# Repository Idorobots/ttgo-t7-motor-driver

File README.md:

# TTGO T7-based DC motor driver board

This is an interface board that adds four DC motor drivers, three servo connectors and I2C breakout to TTGO T7. 
You can use it to build a drone. :shrug:

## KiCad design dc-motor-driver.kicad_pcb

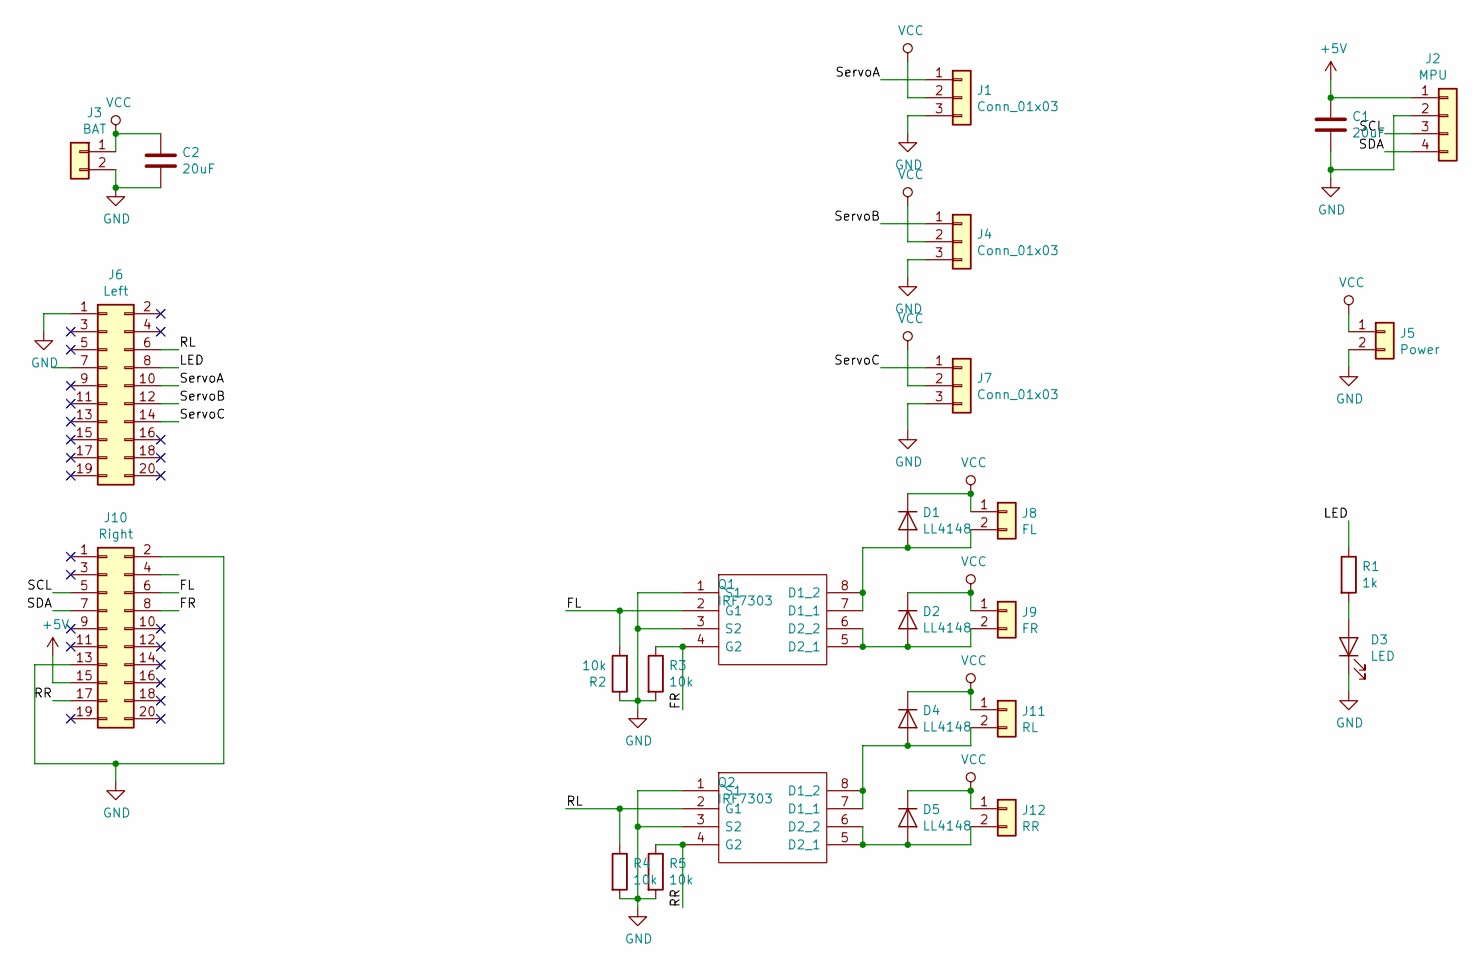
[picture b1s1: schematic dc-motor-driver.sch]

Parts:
C1: 20uF; C_1206_3216Metric_Pad1.42x1.75mm_HandSolder
C2: 20uF; CP_EIA-3528-21_Kemet-B_Pad1.50x2.35mm_HandSolder
D1, D2, D4, D5: LL4148; D_MiniMELF
D3: LED; LED_1206_3216Metric_Pad1.42x1.75mm_HandSolder
J1, J4, J7: Conn_01x03; PinHeader_1x03_P2.54mm_Vertical
J2: MPU; PinHeader_1x04_P2.54mm_Vertical
J3: BAT; JST_XH_S2B-XH-A-1_1x02_P2.50mm_Horizontal
J5: Power; PinHeader_1x02_P2.54mm_Vertical
J6: Left; PinHeader_2x10_P2.54mm_Vertical
J8: FL; Molex_PicoBlade_53398-0271_1x02-1MP_P1.25mm_Vertical
J9: FR; Molex_PicoBlade_53398-0271_1x02-1MP_P1.25mm_Vertical
J10: Right; PinHeader_2x10_P2.54mm_Vertical
J11: RL; Molex_PicoBlade_53398-0271_1x02-1MP_P1.25mm_Vertical
J12: RR; Molex_PicoBlade_53398-0271_1x02-1MP_P1.25mm_Vertical
Q1, Q2: IRF7303; SOIC-8_3.9x4.9mm_P1.27mm
R1: 1k; R_1206_3216Metric
R2, R3, R4, R5: 10k; R_1206_3216Metric

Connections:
+5V: C1.1, J2.1, J10.15
/FL: J10.6, Q1.2 (G1), R2.2
/FR: J10.8, Q1.4 (G2), R3.1
/LED: J6.8, R1.1
/RL: J6.6, Q2.2 (G1), R4.1
/RR: J10.17, Q2.4 (G2), R5.1
/SCL: J2.3, J10.5
/SDA: J2.4, J10.7
/ServoA: J1.1, J6.10
/ServoB: J4.1, J6.12
/ServoC: J6.14, J7.1
GND: C1.2, C2.2, D3.1 (K), J1.3, J2.2, J3.2, J4.3, J5.2, J6.1, J7.3, J8.MP, J9.MP, J10.2, J10.13, J11.MP, J12.MP, Q1.1 (S1), Q1.3 (S2), Q2.1 (S1), Q2.3 (S2), R2.1, R3.2, R4.2, R5.2
unnamed: D1.2 (A), J8.2, Q1.7 (D1_1), Q1.8 (D1_2)
unnamed: D2.2 (A), J9.2, Q1.5 (D2_1), Q1.6 (D2_2)
unnamed: D3.2 (A), R1.2
unnamed: D4.2 (A), J11.2, Q2.7 (D1_1), Q2.8 (D1_2)
unnamed: D5.2 (A), J12.2, Q2.5 (D2_1), Q2.6 (D2_2)
VCC: C2.1, D1.1 (K), D2.1 (K), D4.1 (K), D5.1 (K), J1.2, J3.1, J4.2, J5.1, J7.2, J8.1, J9.1, J11.1, J12.1

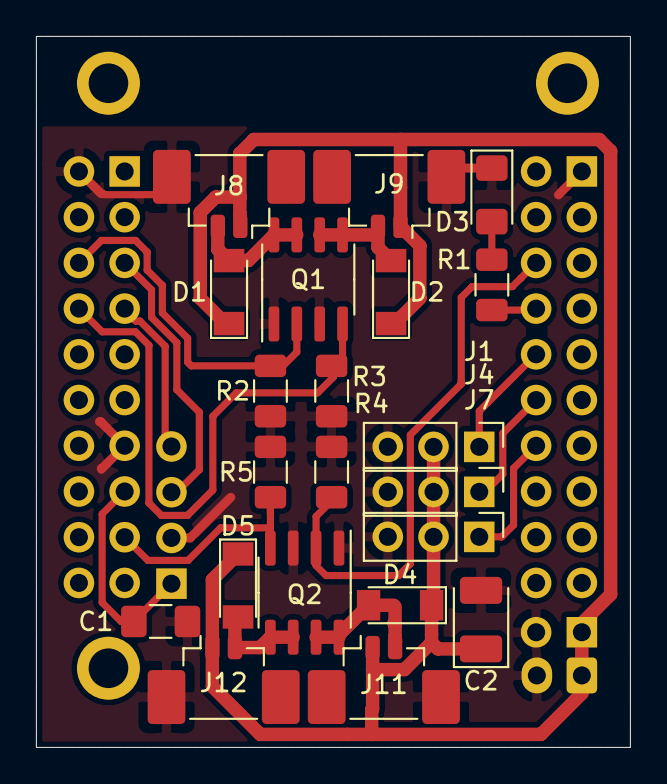
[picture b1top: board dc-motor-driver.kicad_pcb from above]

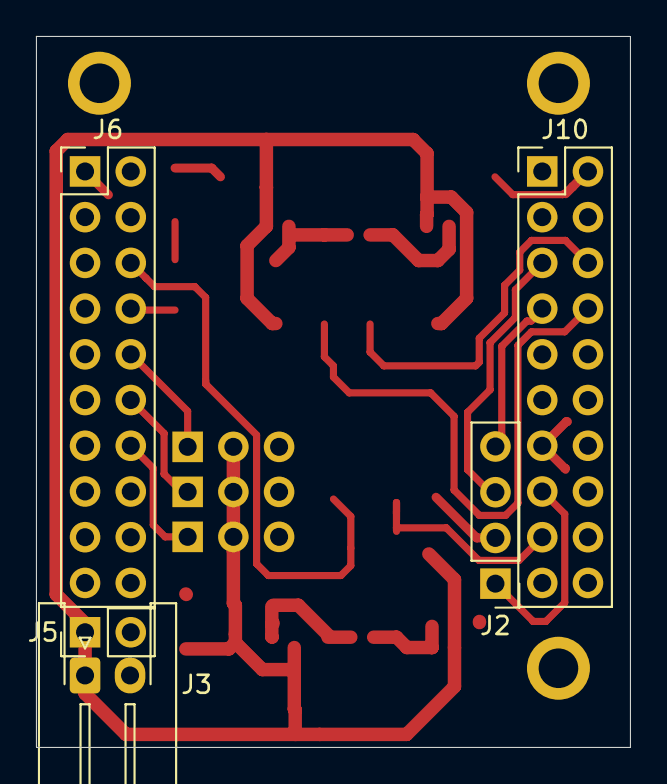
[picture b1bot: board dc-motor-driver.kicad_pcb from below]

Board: 2 copper layers, 33.0 x 39.5 mm, 26 parts (5 on the bottom side), 18 nets.

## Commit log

2019-11-07 Save it before it's too late.
2019-12-03 Redesigned the board to work with TTGO T7 modules.
2019-12-04 Added a third servo and an LED.
2019-12-04 Improved the ground plane.
2019-12-04 Adjusted the silkscreen.
2019-12-04 Changed the molex connectors to the vertical version.
2019-12-04 Made the battery connector horizontal.
2019-12-04 Aligned the pin headers some more.
2019-12-11 Moved the PCB to a more convenient location.
2019-12-11 Moved servos & led pins to output-enabled pins.
2019-12-11 Changed the power source for the MPU.
2019-12-11 Removed an unused wire.
2019-12-11 Added README.
